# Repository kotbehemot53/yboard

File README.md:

# yboard
A keyboard pretending to be a joystick for classic home microcomputers

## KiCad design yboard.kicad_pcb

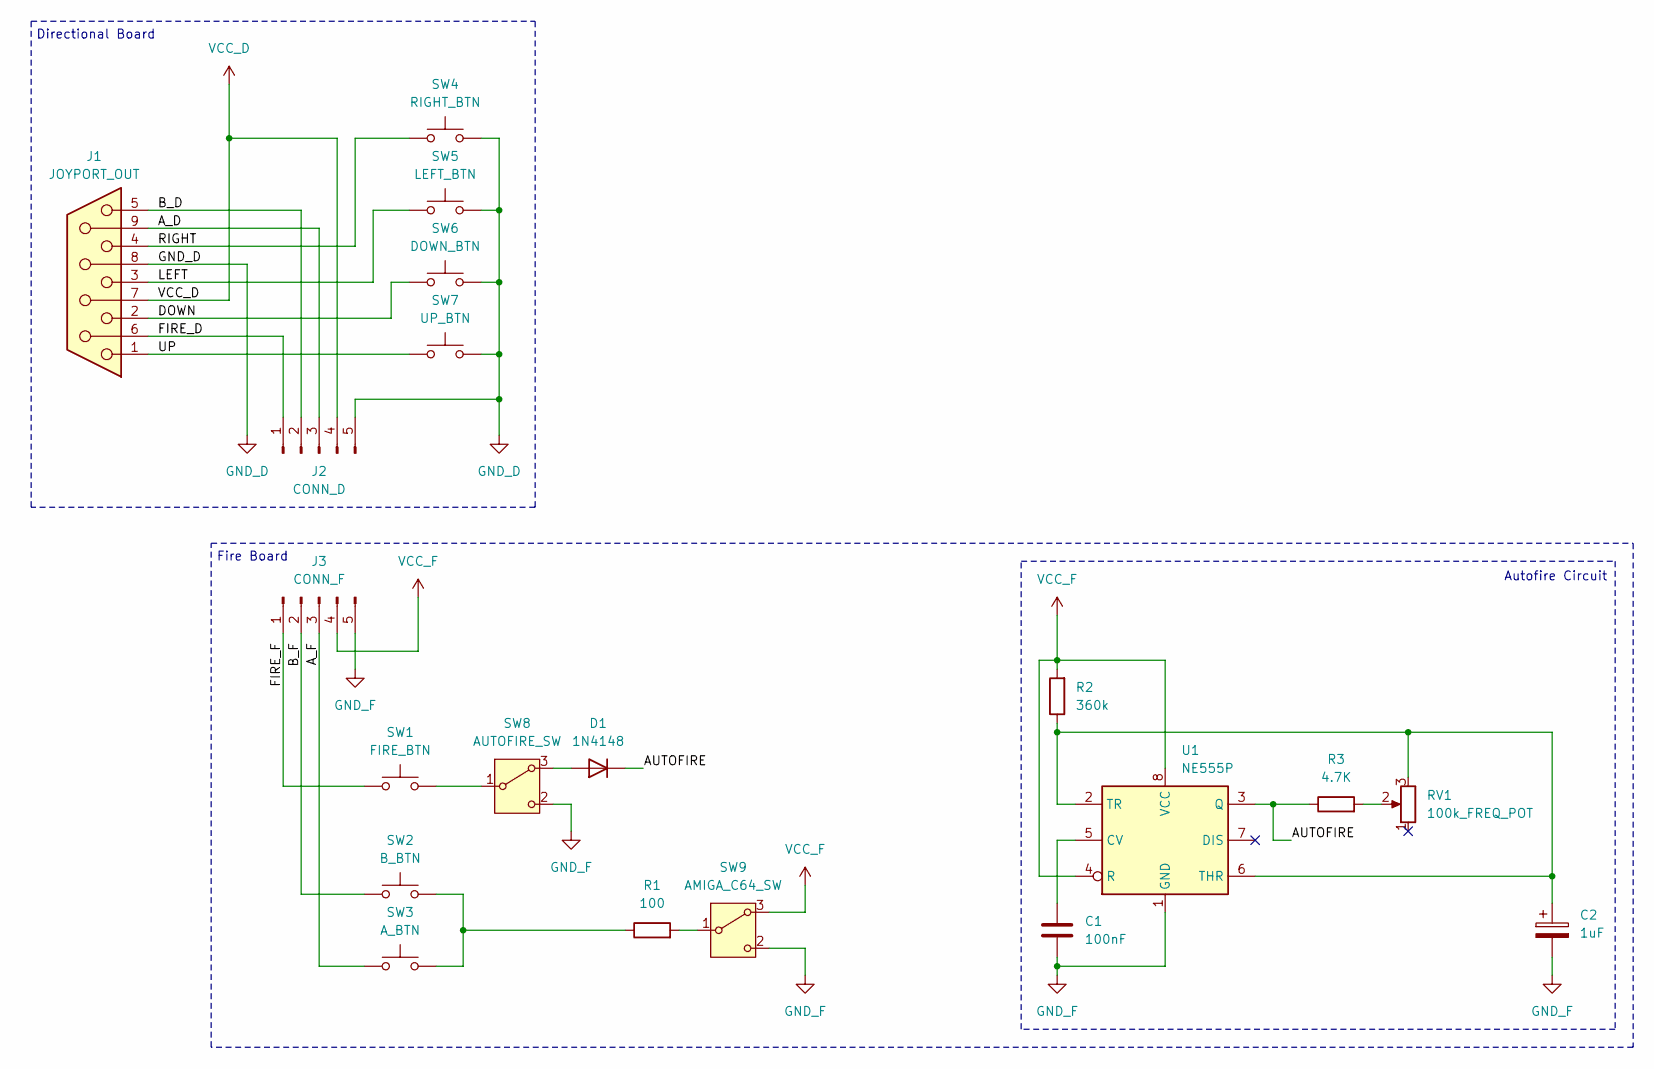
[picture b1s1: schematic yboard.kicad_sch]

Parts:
C1: 100nF; C_Disc_D4.7mm_W2.5mm_P5.00mm
C2: 1uF; CP_Radial_D5.0mm_P2.50mm
D1: 1N4148; D_DO-35_SOD27_P7.62mm_Horizontal
J1: JOYPORT_OUT; JST_XH_S9B-XH-A_1x09_P2.50mm_Horizontal
J2: CONN_D; JST_XH_S5B-XH-A_1x05_P2.50mm_Horizontal
J3: CONN_F; JST_XH_S5B-XH-A_1x05_P2.50mm_Horizontal
R1: 100; R_Axial_DIN0207_L6.3mm_D2.5mm_P7.62mm_Horizontal
R2: 360k; R_Axial_DIN0207_L6.3mm_D2.5mm_P7.62mm_Horizontal
R3: 4.7K; R_Axial_DIN0207_L6.3mm_D2.5mm_P7.62mm_Horizontal
RV1: 100k_FREQ_POT; Potentiometer_Piher_T-16H_Single_Horizontal
SW1: FIRE_BTN; SW_MX
SW2: B_BTN; SW_MX
SW3: A_BTN; SW_MX
SW4: RIGHT_BTN; SW_MX
SW5: LEFT_BTN; SW_MX
SW6: DOWN_BTN; SW_MX
SW7: UP_BTN; SW_MX
SW8: AUTOFIRE_SW; SS12T44_SLIDER_SWITCH_SPDT
SW9: AMIGA_C64_SW; SS12T44_SLIDER_SWITCH_SPDT
U1: NE555P; DIP-8_W7.62mm

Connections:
/AUTOFIRE: D1.1 (K), R3.1, U1.3 (Q)
/A_D: J1.9, J2.3
/A_F: J3.3, SW3.1
/B_D: J1.5, J2.2
/B_F: J3.2, SW2.1
/DOWN: J1.2, SW6.1
/FIRE_D: J1.6, J2.1
/FIRE_F: J3.1, SW1.1
/LEFT: J1.3, SW5.1
/RIGHT: J1.4, SW4.1
/UP: J1.1, SW7.1
GND_D: J1.8, J2.5, SW4.2, SW5.2, SW6.2, SW7.2
GND_F: C1.2, C2.2, J3.5, SW8.2 (C), SW9.2 (C), U1.1 (GND)
unnamed: D1.2 (A), SW8.3 (A)
unnamed: R1.1, SW2.2, SW3.2
unnamed: R3.2, RV1.2
unnamed: SW1.2, SW8.1 (B)
unnamed: R1.2, SW9.1 (B)
unnamed: C1.1, U1.5 (CV)
unnamed: C2.1, R2.1, RV1.3, U1.2 (TR), U1.6 (THR)
VCC_D: J1.7, J2.4
VCC_F: J3.4, R2.2, SW9.3 (A), U1.4 (R), U1.8 (VCC)

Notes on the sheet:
Fire Board
Directional Board
Autofire Circuit

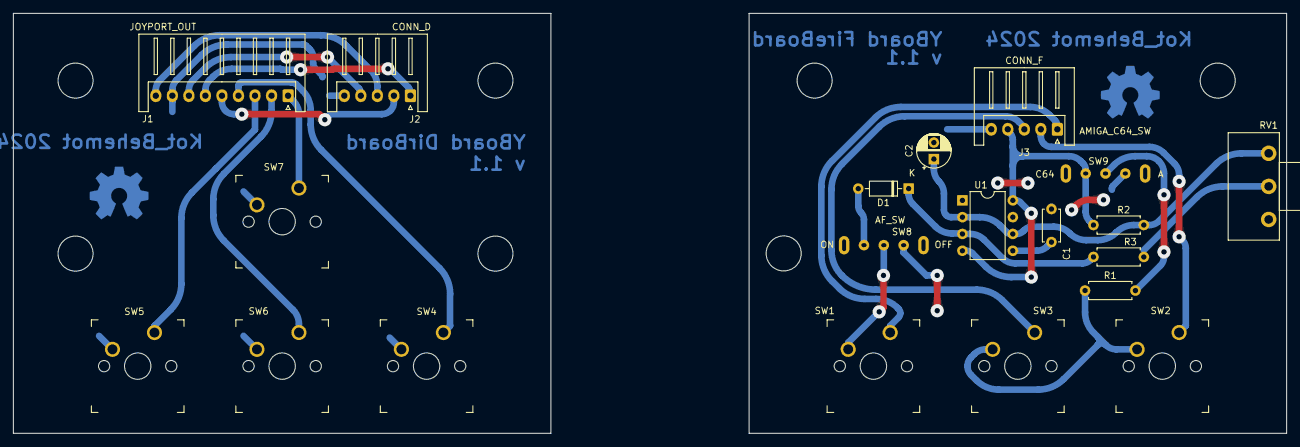
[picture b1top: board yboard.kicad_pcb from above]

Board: 2 copper layers, 192.5 x 63.5 mm, 20 parts (0 on the bottom side), 22 nets.

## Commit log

2024-07-11 initial design
2024-07-11 boards separated
2024-07-11 first complete design
2024-07-11 gitignore
2024-07-12 fill tweaks
2024-07-12 m3 mounting holes swapped for m5 holes (to accommodate a post with m3 screw going through)
2024-07-12 cosmetics
2024-07-12 unnecessary jumpers removed, cosmetics
2024-07-12 silly text
2024-07-12 rounded traces & teardrops
2024-07-13 footprints cleanup - kailh copied to local footprints dir
2024-07-13 post-drc
2024-07-13 additional drill marks
2024-07-13 font change, fab file
2024-07-13 cosmetics, logos
2024-07-18 dir buttons moved closer together
2024-07-22 more button movement
2024-07-28 A rename to Yboard
2024-07-28 YBoard rename within the designs
2024-07-28 only the board with rounded traces retained
2024-07-28 labeling, libraries and other minor fixes
2024-07-28 3d models updated
2024-07-28 footprint number fix
2024-07-28 v number update
2024-07-29 step files added to connector models for 3d export
